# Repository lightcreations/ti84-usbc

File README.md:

# ti84-usbc
PCB files for the TI84 USBC mod PCB

This PCB should 1.2mm or less thick

Video: https://www.youtube.com/watch?v=36iKaN4QcAg

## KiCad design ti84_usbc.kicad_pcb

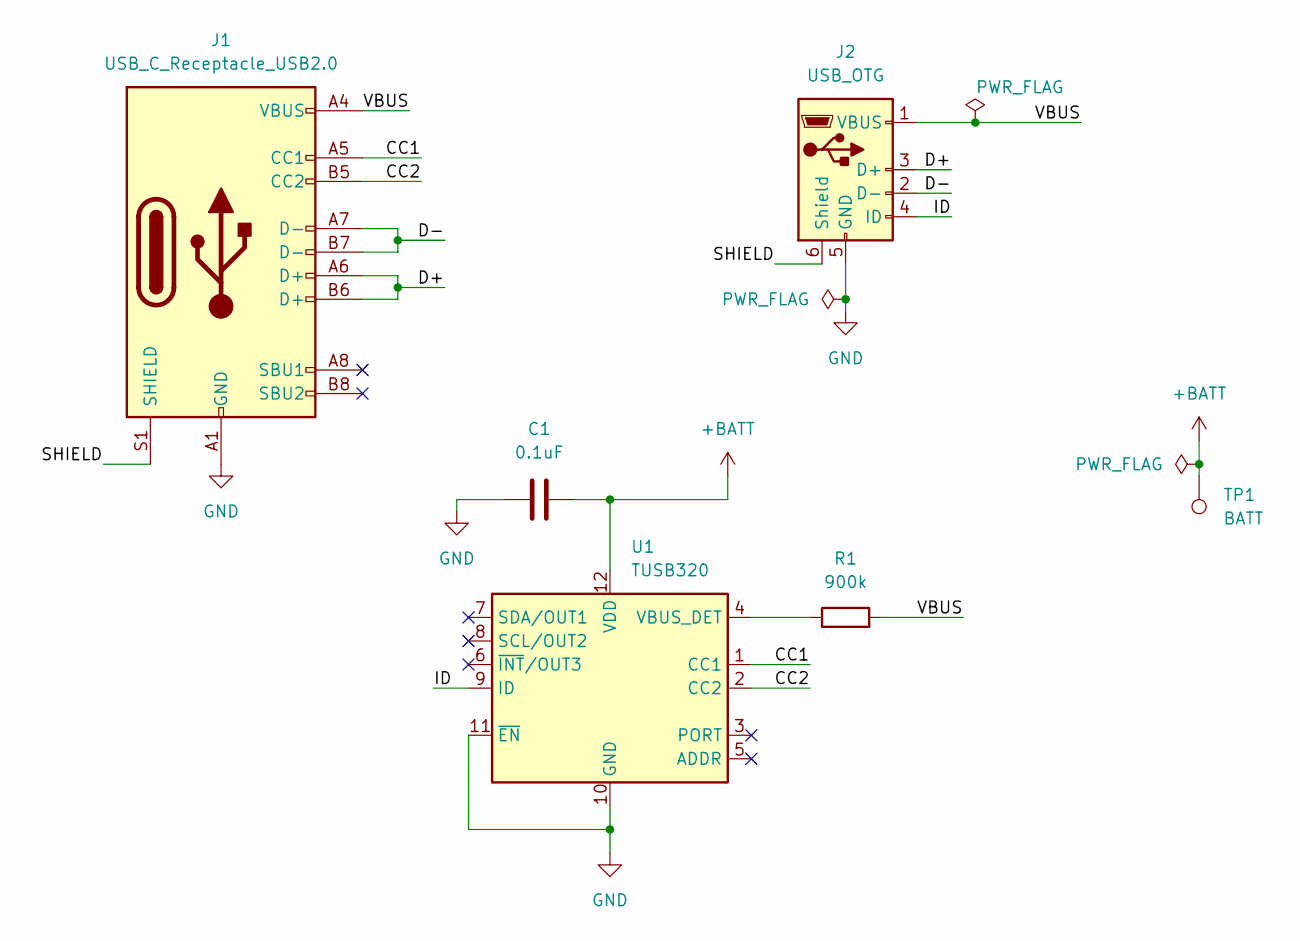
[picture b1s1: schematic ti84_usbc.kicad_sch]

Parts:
C1: 0.1uF; C_0402_1005Metric
J1: USB_C_Receptacle_USB2.0; USB_C_Receptacle_GCT_USB4105-xx-A_16P_TopMnt_Horizontal
J2: USB_OTG; ti84_mini_usb
R1: 900k; R_0402_1005Metric
TP1: BATT; TestPoint_Pad_1.0x1.0mm
U1: TUSB320; IC_TUSB320IRWBR

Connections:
+BATT: C1.2, TP1.1, U1.12 (VDD)
/CC1: J1.A5 (CC1), U1.1 (CC1)
/CC2: J1.B5 (CC2), U1.2 (CC2)
/D+: J1.A6 (D+), J1.B6 (D+), J2.3 (D+)
/D-: J1.A7 (D-), J1.B7 (D-), J2.2 (D-)
/ID: J2.4 (ID), U1.9 (ID)
/SHIELD: J1.S1 (SHIELD), J2.6 (Shield)
/VBUS: J1.A4 (VBUS), J1.A9 (VBUS), J1.B4 (VBUS), J1.B9 (VBUS), J2.1 (VBUS), R1.2
GND: C1.1, J1.A1 (GND), J1.A12 (GND), J1.B1 (GND), J1.B12 (GND), J2.5 (GND), U1.10 (GND), U1.11 (~EN)
unnamed: R1.1, U1.4 (VBUS_DET)

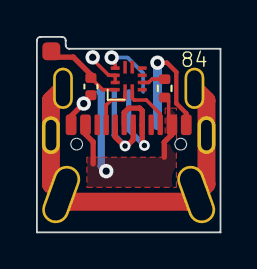
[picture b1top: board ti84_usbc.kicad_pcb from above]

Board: 2 copper layers, 10.2 x 10.9 mm, 6 parts (1 on the bottom side), 10 nets.

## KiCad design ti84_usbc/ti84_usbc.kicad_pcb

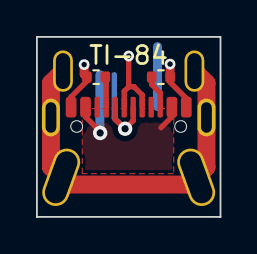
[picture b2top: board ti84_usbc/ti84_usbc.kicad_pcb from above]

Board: 2 copper layers, 10.2 x 10.0 mm, 4 parts (1 on the bottom side), 7 nets.

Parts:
J1: USB_OTG; ti84_mini_usb
J2: USB_C_Receptacle_USB2.0; usb4105
R1, R2: 5.1k; R_0402_1005Metric

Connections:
/D+: J1.3 (D+), J2.A6 (D+), J2.B6 (D+)
/D-: J1.2 (D-), J2.A7 (D-), J2.B7 (D-)
/SHIELD: J1.6 (Shield), J2.S1 (SHIELD)
/VBUS: J1.1 (VBUS), J2.A4 (VBUS), J2.B4 (VBUS), J2.B9 (VBUS)
GND: J1.5 (GND), J2.A12 (GND), J2.B12 (GND), R1.2, R2.2
unnamed: J2.A5 (CC1), R1.1
unnamed: J2.B5 (CC2), R2.1

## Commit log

2023-11-27 Add images
2023-12-02 add v2
2024-02-09 Add files via upload
    Updated PCB to use copper pours for GND and VBUS, used 0.3mm traces instead of 0.2mm, and added a silkscreen label on the PCB since I intend on using this footprint to make a version for the TI-Nspir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
2024-03-06 Add files via upload
    Uploaded boardview file and PDF version of the schematic.
2024-03-12 Add files via upload
    Added Boardview file with OpenBoardData file.
